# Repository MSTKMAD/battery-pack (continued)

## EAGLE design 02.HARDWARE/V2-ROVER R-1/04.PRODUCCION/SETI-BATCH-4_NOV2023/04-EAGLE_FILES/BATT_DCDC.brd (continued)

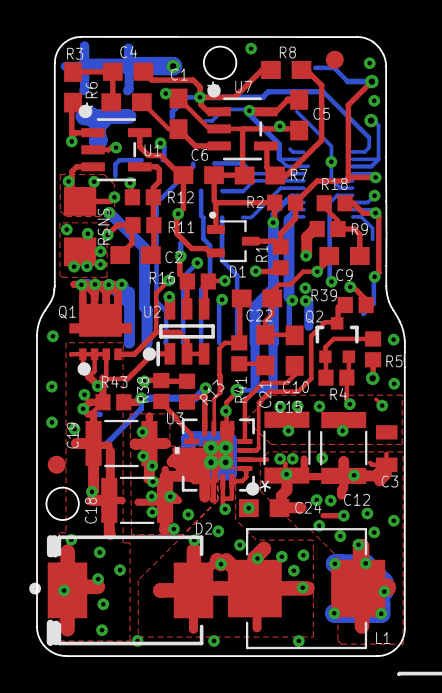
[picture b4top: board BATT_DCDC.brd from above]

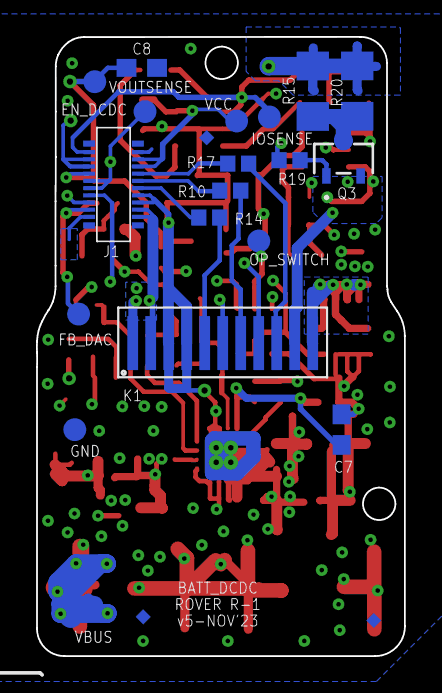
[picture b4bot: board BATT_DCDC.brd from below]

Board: 4 copper layers, 20.4 x 34.4 mm, 67 parts (22 on the bottom side), 36 nets.

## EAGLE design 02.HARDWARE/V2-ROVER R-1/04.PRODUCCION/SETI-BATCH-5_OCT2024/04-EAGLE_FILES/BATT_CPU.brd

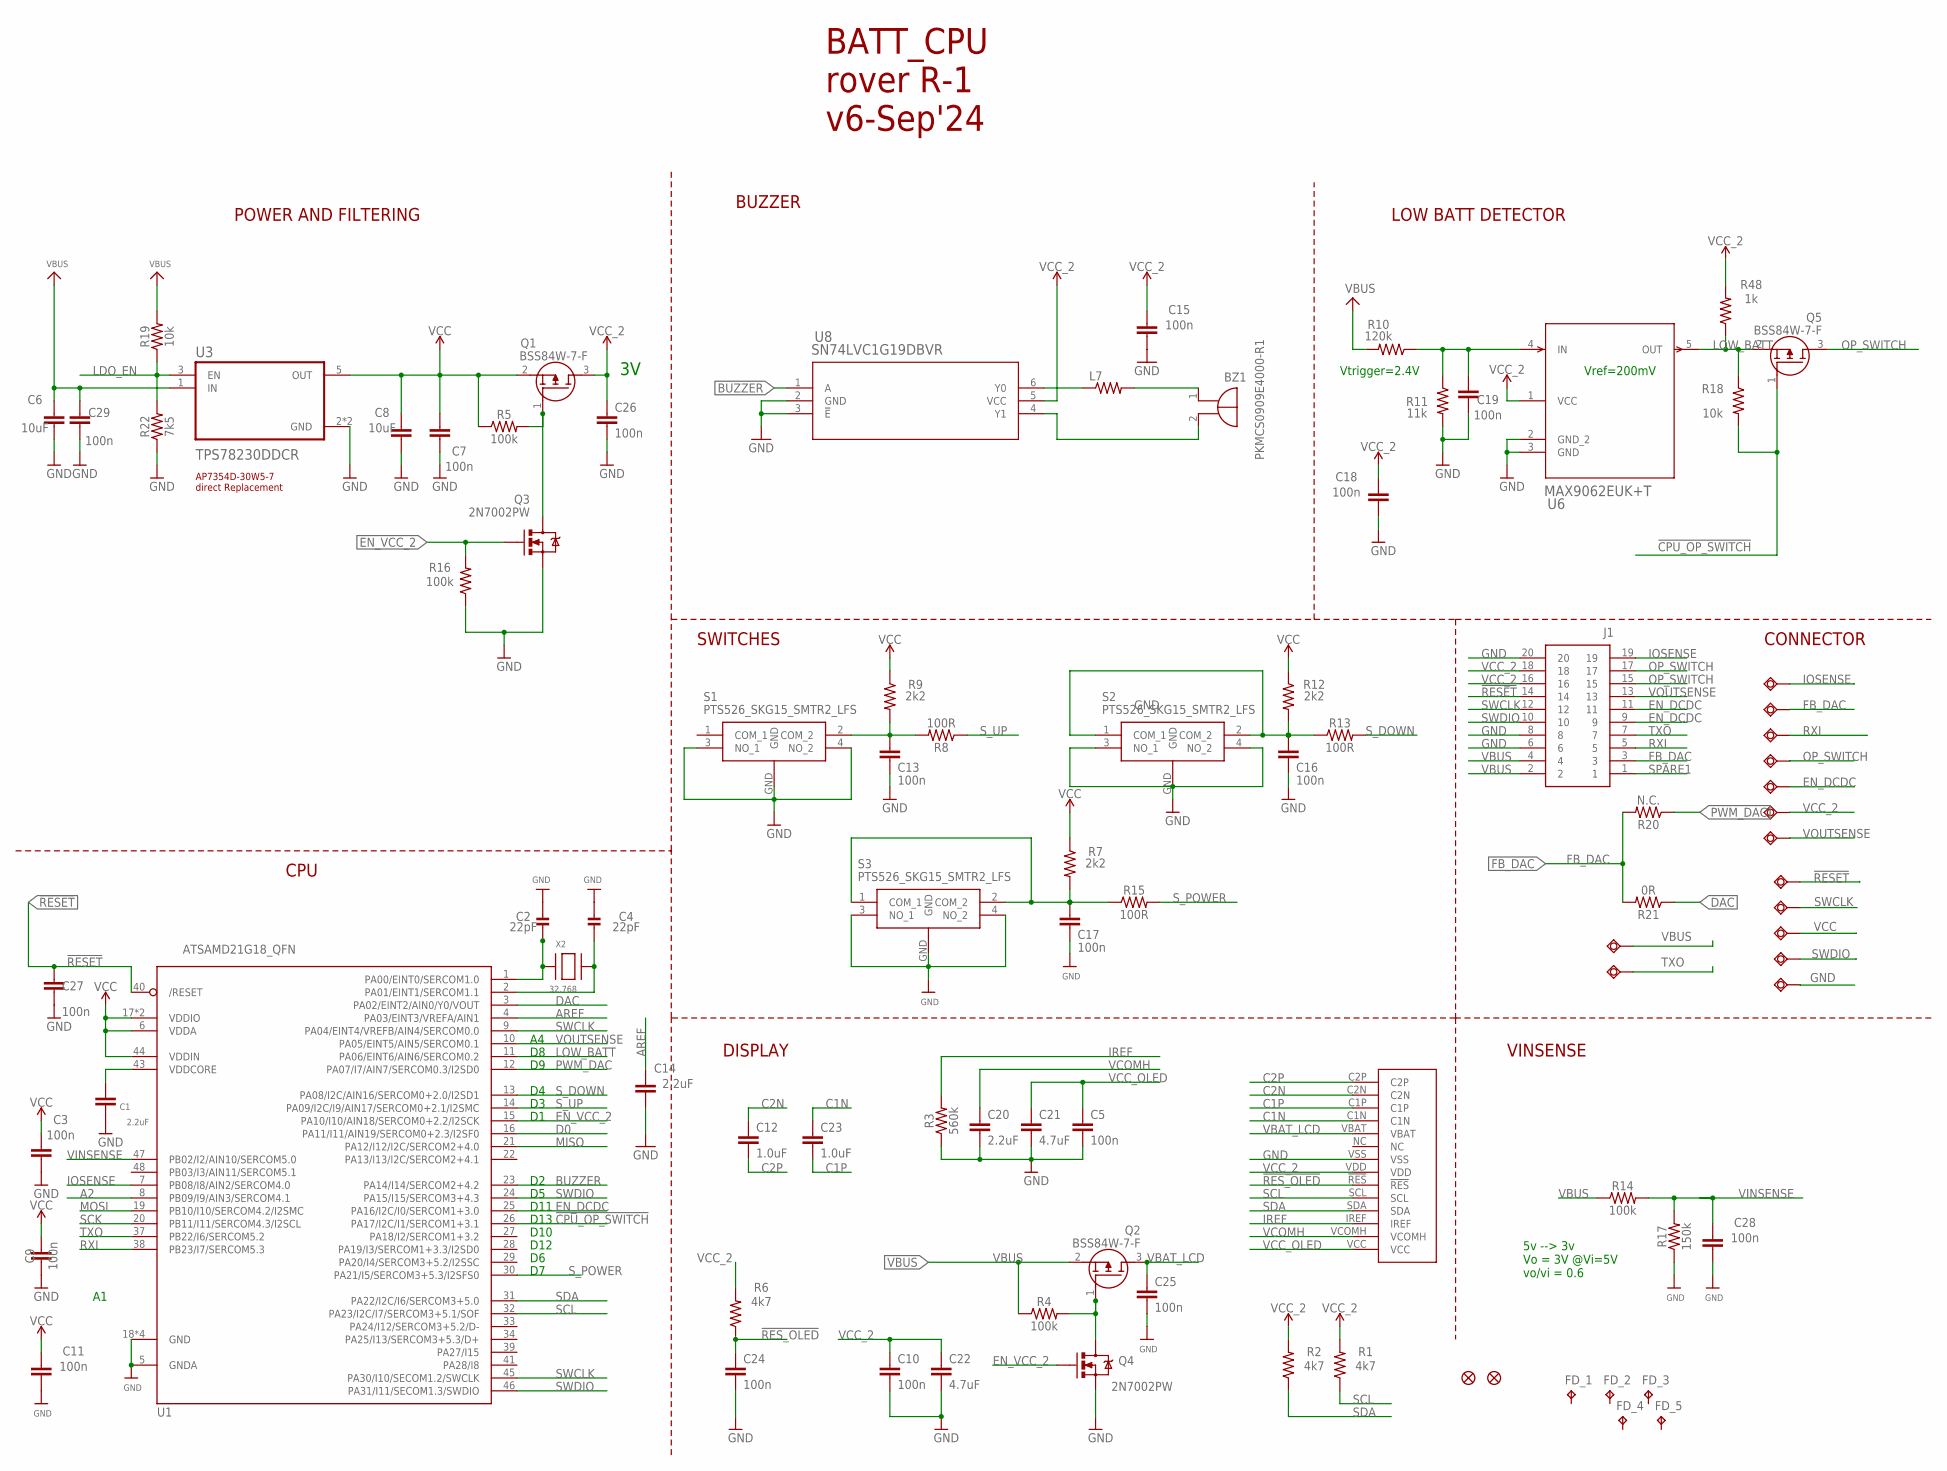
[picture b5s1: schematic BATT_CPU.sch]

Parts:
BZ1: PKMCS0909E4000-R1; PKMCS0909
C1, C14, C20: 2.2uF; 0603
C2, C4: 22pF; 0603-NO
C3, C5, C7, C9, C10, C11, C13, C15, C16, C17, C18, C19, C24, C25, C26, C27, C28, C29: 100n; 0402
C6, C8: 10uF; 0603
C12, C23: 1.0uF; 0402
C21, C22: 4.7uF; 0603
EN_DCDC: TESTPAD_TPSQB1,27; TESTPAD_B1,27
FB_DAC: TESTPAD_TPSQB1,27; TESTPAD_B1,27
FD_1, FD_2, FD_3, FD_4, FD_5: FD_1; TP06SQ
IOSENSE: TESTPAD_TPSQB1,27; TESTPAD_B1,27
J1: DF40C_2.0_-20DS-0.4V_51_; DF40C2020DS04V51
L7: MMZ2012Y202BT000; 0805
OP_SWITCH: TESTPAD_TPSQB1,27; TESTPAD_B1,27
Q1, Q2, Q5: BSS84W-7-F; SOT65P222X110-3N
Q3, Q4: 2N7002PW; SOT323
R1, R2, R6: 4k7; 0402
R3: 560k; 0402
R4, R5, R14, R16: 100k; 0402
R7, R9, R12: 2k2; 0402
R8, R13, R15: 100R; 0402
R10: 120k; 0402
R11: 11k; 0402
R17: 150k; 0402
R18, R19: 10k; 0402
R20: N.C.; 0402
R21: 0R; 0402
R22: 7k5; 0402
R48: 1k; 0402
RXI: TESTPAD_TPSQB1,27; TESTPAD_B1,27
S1, S2, S3: PTS526_SKG15_SMTR2_LFS; PTS526SKG15SMTR2LFS
U1: ATSAMD21G18_QFN; TQFN48_7MM
U3: TPS78230DDCR; SOT95P280X110-5N
U6: MAX9062EUK+T; 21-0057F_MXM
U8: SN74LVC1G19DBVR; DBV6
U$30: 64X32_OLED_049; LCD_14_PINS
U$34, U$35: FIDUCIAL""; FIDUCIAL_1MM
VBUS, VBUS1, VBUS2, VBUS3, VBUS4, VBUS5, VBUS6: TESTPAD_TPSQB1,27; TESTPAD_B1,27
VCC_2: TESTPAD_TPSQB1,27; TESTPAD_B1,27
VOUTSENSE: TESTPAD_TPSQB1,27; TESTPAD_B1,27
X2: 32.768; XTAL3215

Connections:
!CPU_OP_SWITCH: Q5.1 (G), R18.2, U1.26 (PA17/I2C/I1/SERCOM1+3.1)
!RESET: C27.1, J1.14, U1.40 (/RESET), VBUS1.TP
!RES_OLED: C24.1, R6.1, U$30.!RES
A2: U1.8 (PB09/I9/AIN3/SERCOM4.1)
AREF: C14.1, U1.4 (PA03/EINT3/VREFA/AIN1)
BUZZER: U1.23 (PA14/I14/SERCOM2+4.2), U8.1 (A)
C1N: C23.1, U$30.C1N
C1P: C23.2, U$30.C1P
C2N: C12.1, U$30.C2N
C2P: C12.2, U$30.C2P
D0: U1.16 (PA11/I11/AIN19/SERCOM0+2.3/I2SF0)
DAC: R21.1, U1.3 (PA02/EINT2/AIN0/Y0/VOUT)
EN_DCDC: EN_DCDC.TP, J1.9, J1.11, U1.25 (PA16/I2C/I0/SERCOM1+3.0)
EN_VCC_2: Q3.1 (G), Q4.1 (G), R16.2, U1.15 (PA10/I10/AIN18/SERCOM0+2.2/I2SCK)
FB_DAC: FB_DAC.TP, J1.3, R20.2, R21.2
GND: C1.2, C2.2, C3.2, C4.2, C5.2, C6.2, C7.2, C8.2, C9.2, C10.2, C11.2, C13.2, C14.2, C15.2, C16.2, C17.2, C18.2, C19.2, C20.2, C21.2, C22.2, C24.2, C25.2, C26.2, C27.2, C28.2, C29.2, J1.6, J1.8, J1.20, Q3.2 (S), Q4.2 (S), R3.1, R11.2, R16.1, R17.1, R22.1, S1.3 (NO_1), S1.4 (NO_2), S1.GND, S2.3 (NO_1), S2.4 (NO_2), S2.GND, S3.3 (NO_1), S3.4 (NO_2), S3.GND, U1.5 (GNDA), U1.18 (GND), U1.35 (GND), U1.42 (GND), U1.THERMAL (GND), U3.2 (GND), U3.4 (GND), U6.2 (GND_2), U6.3 (GND), U8.2 (GND), U8.3 (!E), U$30.VSS, VBUS4.TP
IOSENSE: IOSENSE.TP, J1.19, U1.7 (PB08/I8/AIN2/SERCOM4.0)
IREF: R3.2, U$30.IREF
LDO_EN: R19.1, R22.2, U3.3 (EN)
LOW_BATT: Q5.2 (S), R18.1, R48.1, U1.11 (PA06/EINT6/AIN6/SERCOM0.2), U6.5 (OUT)
MISO: U1.21 (PA12/I12/I2C/SERCOM2+4.0)
MOSI: U1.19 (PB10/I10/SERCOM4.2/I2SMC)
unnamed: C17.1, R7.2, R15.1, S3.1 (COM_1), S3.2 (COM_2)
unnamed: C13.1, R8.2, R9.2, S1.2 (COM_2)
unnamed: C16.1, R12.2, R13.1, S2.1 (COM_1), S2.2 (COM_2)
unnamed: Q2.1 (G), Q4.3 (D), R4.2
unnamed: C2.1, U1.1 (PA00/EINT0/SERCOM1.0), X2.P$1
unnamed: Q1.1 (G), Q3.3 (D), R5.2
unnamed: C4.1, U1.2 (PA01/EINT1/SERCOM1.1), X2.P$2
unnamed: C19.1, R10.1, R11.1, U6.4 (IN)
unnamed: L7.1, U8.6 (Y0)
unnamed: BZ1.1 (+), L7.2
unnamed: BZ1.2 (-), U8.4 (Y1)
OP_SWITCH: J1.15, J1.17, OP_SWITCH.TP, Q5.3 (D)
PWM_DAC: R20.1, U1.12 (PA07/I7/AIN7/SERCOM0.3/I2SD0)
RXI: J1.5, RXI.TP, U1.38 (PB23/I7/SERCOM5.3)
SCK: U1.20 (PB11/I11/SERCOM4.3/I2SCL)
SCL: R1.1, U1.32 (PA23/I2C/I7/SERCOM3+5.1/SOF), U$30.SCL
SDA: R2.1, U1.31 (PA22/I2C/I6/SERCOM3+5.0), U$30.SDA
SPARE1: J1.1
SWCLK: J1.12, U1.9 (PA04/EINT4/VREFB/AIN4/SERCOM0.0), U1.45 (PA30/I10/SECOM1.2/SWCLK), VBUS2.TP
SWDIO: J1.10, U1.24 (PA15/I15/SERCOM3+4.3), U1.46 (PA31/I11/SECOM1.3/SWDIO), VBUS3.TP
S_DOWN: R13.2, U1.13 (PA08/I2C/AIN16/SERCOM0+2.0/I2SD1)
S_POWER: R15.2, U1.30 (PA21/I5/SERCOM3+5.3/I2SFS0)
S_UP: R8.1, U1.14 (PA09/I2C/I9/AIN17/SERCOM0+2.1/I2SMC)
TXO: J1.7, U1.37 (PB22/I6/SERCOM5.2), VBUS6.TP
VBAT_LCD: C25.1, Q2.3 (D), U$30.VBAT
VBUS: C6.1, C29.1, J1.2, J1.4, Q2.2 (S), R4.1, R10.2, R14.1, R19.2, U3.1 (IN), VBUS5.TP
VCC: C3.1, C7.1, C8.1, C9.1, C11.1, Q1.2 (S), R5.1, R7.1, R9.1, R12.1, R48.2, U1.6 (VDDA), U1.17 (VDDIO), U1.36 (VDDIO), U1.44 (VDDIN), U3.5 (OUT), VBUS.TP
VCC_2: C10.1, C15.1, C18.1, C22.1, C26.1, J1.16, J1.18, Q1.3 (D), R1.2, R2.2, R6.2, U6.1 (VCC), U8.5 (VCC), U$30.VDD, VCC_2.TP
VCC_OLED: C5.1, C21.1, U$30.VCC
VCOMH: C20.1, U$30.VCOMH
VDDCORE: C1.1, U1.43 (VDDCORE)
VINSENSE: C28.1, R14.2, R17.2, U1.47 (PB02/I2/AIN10/SERCOM5.0)
VOUTSENSE: J1.13, U1.10 (PA05/EINT5/AIN5/SERCOM0.1), VOUTSENSE.TP

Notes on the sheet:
POWER AND FILTERING
BUZZER
AP7354D-30W5-7 direct Replacement
D10
LOW BATT DETECTOR
CPU
Vref=200mV
Vtrigger=2.4V
D13
D11
D12
5v --> 3v Vo = 3V @Vi=5V vo/vi = 0.6
BATT_CPU rover R-1 v6-Sep'24
DISPLAY
SWITCHES
CONNECTOR
VINSENSE

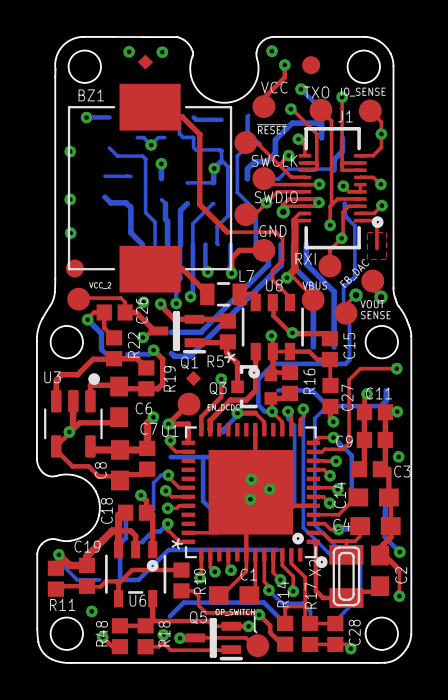
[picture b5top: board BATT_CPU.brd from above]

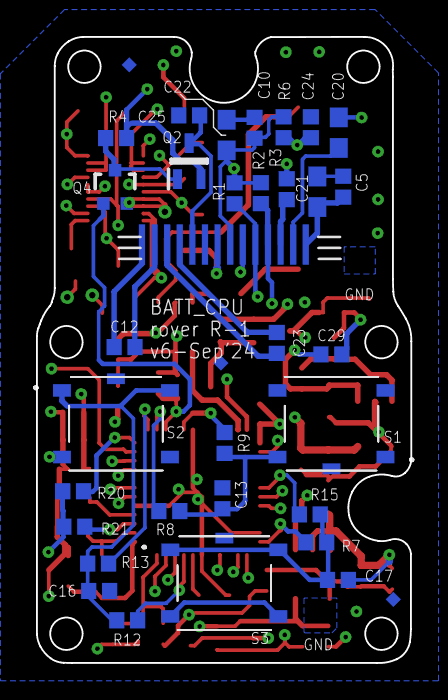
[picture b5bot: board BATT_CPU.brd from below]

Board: 4 copper layers, 20.8 x 34.8 mm, 90 parts (35 on the bottom side), 49 nets.
